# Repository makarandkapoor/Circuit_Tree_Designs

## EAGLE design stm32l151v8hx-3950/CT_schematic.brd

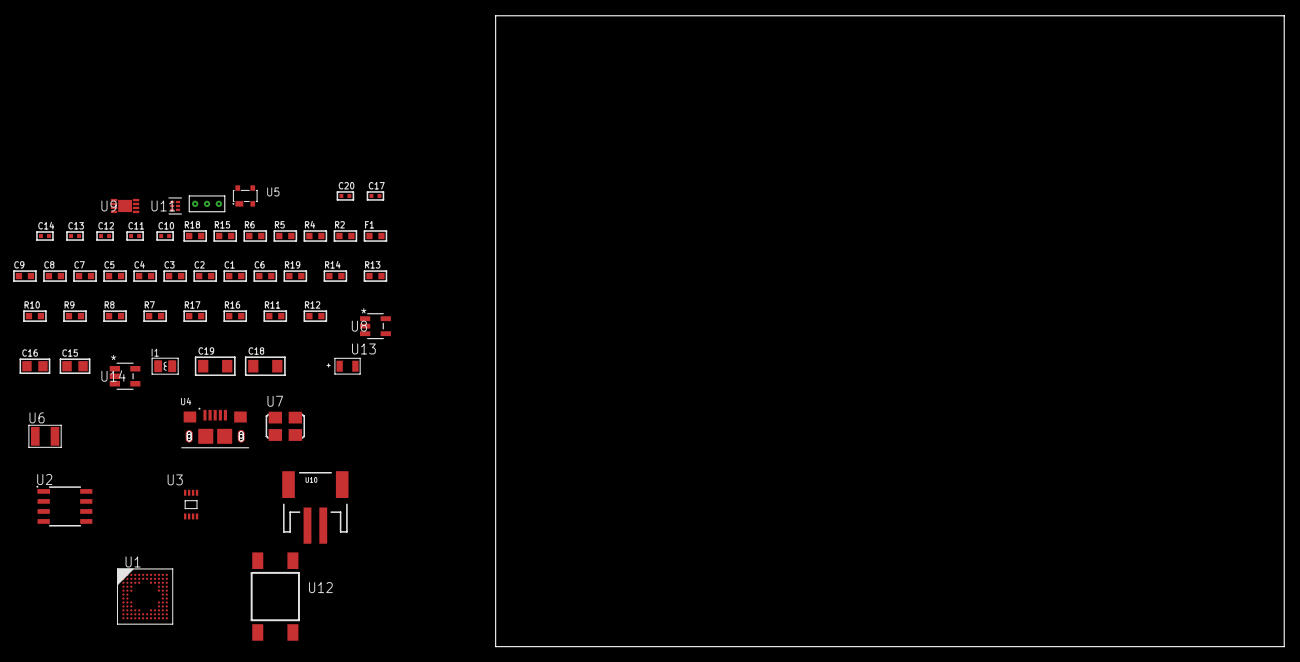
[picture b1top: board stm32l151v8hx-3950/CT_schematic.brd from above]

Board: 2 copper layers, 54 parts (0 on the bottom side), 32 nets, no tracks yet.

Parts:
C1, C2, C3, C4, C5, C7: 1e-07; C0603
C6: 4.7e-06; C0603
C8: 1e-08; C0603
C9: 1e-06; C0603
C10, C11: 1e-11; C0402
C12, C13, C14, C20: 1e-08; C0402
C15, C16: 1e-05; C0805
C17: 1e-07; C0402
C18, C19: 1e-05; C1206
F1: 240.0; L0603
I1: 3.3e-06; L0806
R2: 1000.0; R0603
R4: 4700.0; R0603
R5, R6: 2200.0; R0603
R7, R8, R9, R10, R13, R14, R19: 10000.0; R0603
R11: 220000.0; R0603
R12: 1000000.0; R0603
R15: 9100.0; R0603
R16: 680000.0; R0603
R17: 120000.0; R0603
R18: 2000.0; R0603
U1: STM32L151V8H6; UFBGA100
U2: AT25256B-SSHL-T; SOIC-8
U3: 24AA01T-I/MNY; TDFN-8/6MM
U4: 10118193-0001LF; FCI_10118193-0001LF
U5: prtr5v0u2ax; SOT143B
U6: ABS07-32.768KHZ-7-T
U7: ASFL1-25MHZ-NCS; ASFL1
U8: ltc3406es5; TSOT-23-5
U9: MCP73831T-2ACI/MC; DFN8_2X3MC
U10: S2B-PH-SM4-TB(LF)(SN); JST-2-SMD
U11: TPS3895ADRYR; SON-6
U12: 4-1437565-2; SW_4-1437565-2
U13: Q65110A2395; LGM67K-G1J2-24-Z
U14: nc7sz125m5x; NC7SZ125M5X
U15: Dummy; DUMMY_PACKAGE_120

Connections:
CLK_CRYSTAL_U1_D1: C10.1, U1.D1, U6.1
CLK_CRYSTAL_U1_E1: C11.1, U1.E1, U6.2
CLK_U1_F1: U1.F1, U7.3
GND: C1.2, C2.2, C3.2, C4.2, C5.2, C6.2, C7.2, C8.2, C9.2, C10.2, C11.2, C12.2, C13.2, C14.2, C15.2, C16.1, C16.2, C17.2, C18.2, C19.2, C20.2, R2.2, R7.2, R11.2, R15.2, R17.2, R18.2, U1.D3, U1.E3, U1.F2, U1.F11, U1.F12, U1.J1, U1.K1, U2.4, U3.4, U3.7, U4.5, U4.6, U4.7, U4.8, U4.9, U5.1, U7.2, U8.2, U9.6, U9.9, U10.2, U11.2, U13.C, U14.1, U14.3, U15.1
INPUT_USBPOWER_5V: C18.1, R19.2, U4.1, U5.4, U9.1, U9.2
NET_U1_A3: R5.1, U1.A3, U3.6
NET_U1_A4: R7.1, U1.A4
NET_U1_B3: R6.1, U1.B3, U3.5
NET_U1_E2: C7.1, U1.E2
NET_U1_H2: R4.1, U1.H2, U14.4
NET_U1_M1: C8.1, C9.1, F1.1, U1.L1, U1.M1
NET_U1_M12: U12.3, U12.4
NET_U2_3: R8.1, U2.3
NET_U2_7: R10.1, U2.7
NET_U8_3: I1.1, U8.3
NET_U8_5: R11.1, R12.1, U8.5
NET_U8_ATNET_3: I1.2, R12.2
NET_U9_5: R19.1, U9.5
NET_U9_8: R18.1, U9.8
NET_U11_1: R14.1, R15.1, U11.1
NET_U11_3: R16.2, R17.1, U11.3
NET_U11_4: R13.1, U11.4, U14.2
NET_U12_1: R2.1, U12.1, U12.2
PROC_ADC_IN20: U1.K11, U15.2
PROC_SPI1_MISO: U1.A7, U2.2
PROC_SPI1_MOSI: U1.C5, U2.5
PROC_SPI1_NSS: R9.1, U1.A9, U2.1
PROC_SPI1_SCK: U1.A8, U2.6
PROC_USB_DM: U1.B12, U4.2, U5.3
PROC_USB_DP: U1.A12, U4.3, U5.2
VCC_S1_3V7: C15.1, C19.1, U8.4, U9.3, U9.4, U10.1
VCC_TIER1_3V3: C1.1, C2.1, C3.1, C4.1, C5.1, C6.1, C12.1, C13.1, C14.1, C16.2, C17.1, C20.1, F1.2, I1.2, R4.2, R5.2, R6.2, R8.2, R9.2, R10.2, R12.2, R13.2, R14.2, R16.1, U1.C4, U1.G2, U1.G11, U1.G12, U1.H3, U2.8, U3.8, U7.4, U11.6, U14.5

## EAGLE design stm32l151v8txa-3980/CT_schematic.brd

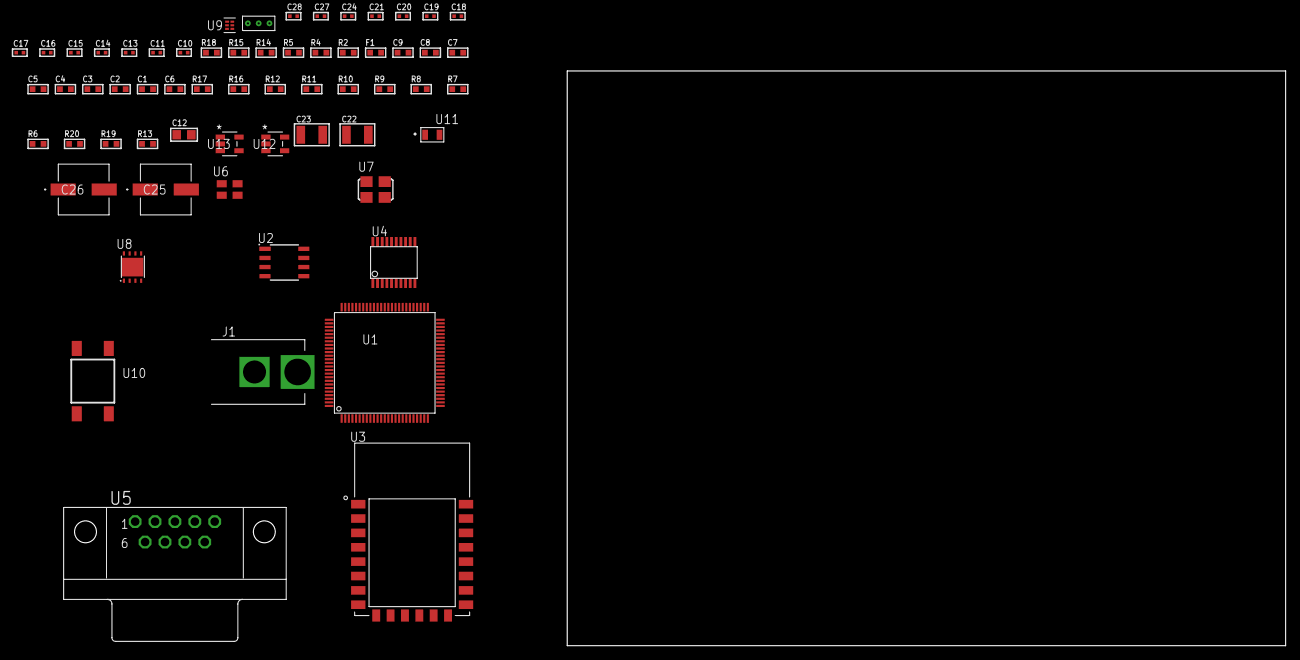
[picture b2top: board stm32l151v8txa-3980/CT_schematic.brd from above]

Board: 2 copper layers, 100.0 x 80.0 mm, 62 parts (0 on the bottom side), 46 nets, no tracks yet.

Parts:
C1, C2, C3, C4, C5, C7: 1e-07; C0603
C6: 4.7e-06; C0603
C8: 1e-08; C0603
C9: 1e-06; C0603
C10, C19, C20, C21, C27, C28: 1e-08; C0402
C11, C13, C14, C15, C16, C17, C18, C24: 1e-07; C0402
C12: 1e-05; C0805
C22, C23: 1e-05; C1210
C25, C26: 0.0001; EXV-9H
F1: 240.0; L0603
J1: PJ-037B; PJ-037B_PACKAGE
R2, R15: 1000.0; R0603
R4, R5: 4700.0; R0603
R6, R7, R8, R9, R10, R11, R12, R16, R17: 10000.0; R0603
R13: 100000.0; R0603
R14: 2231.0; R0603
R18: 9100.0; R0603
R19: 680000.0; R0603
R20: 120000.0; R0603
U1: STM32L151V8T6A; LQFP100
U2: AT25128B-SSHL-T; SOIC-8
U3: ESP8266-12E
U4: SP3203ECY-L/TR; TSSOP20-I
U5: 182-009-113R531; 182-009-MALE
U6: ASEK-32.768KHz-ECST; ASEK
U7: ASFL1-25MHZ-NCS; ASFL1
U8: LP3878SDX-ADJ/NOPB; WSON-8
U9: TPS3895ADRYR; SON-6
U10: 4-1437565-2; SW_4-1437565-2
U11: Q65110A2395; LGM67K-G1J2-24-Z
U12, U13: nc7sz125m5x; NC7SZ125M5X
U14: Dummy; DUMMY_PACKAGE_135

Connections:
CLK_U1_8: U1.8, U6.3
CLK_U1_12: U1.12, U7.3
GND: C1.2, C2.2, C3.2, C4.2, C5.2, C6.2, C7.2, C8.2, C9.2, C10.2, C11.2, C12.2, C13.2, C14.2, C17.2, C18.2, C19.2, C20.2, C21.2, C22.2, C23.2, C24.2, C25.2, C26.2, C27.2, C28.2, J1.2, R2.2, R6.2, R12.2, R15.2, R18.2, R20.2, U1.10, U1.19, U1.20, U1.27, U1.49, U1.74, U1.99, U2.4, U3.15, U4.18, U5.5, U6.2, U7.2, U8.3, U8.PAD, U9.2, U11.C, U12.1, U12.3, U13.1, U13.3, U14.1
NET_U1_6: C7.1, U1.6
NET_U1_14: R5.1, U1.14, U13.4
NET_U1_22: C8.1, C9.1, F1.1, U1.21, U1.22
NET_U1_94: R6.1, U1.94
NET_U1_98: U10.3, U10.4
NET_U2_3: R7.1, U2.3
NET_U2_7: R9.1, U2.7
NET_U3_1: R4.1, U3.1, U12.4
NET_U3_3: R10.1, U3.3
NET_U3_18: R11.1, U3.18
NET_U4_1: C15.1, U4.1
NET_U4_2: C17.1, U4.2
NET_U4_3: C15.2, U4.3
NET_U4_4: C16.1, U4.4
NET_U4_5: C16.2, U4.5
NET_U4_6: C18.1, U4.6
NET_U5_2: U4.14, U5.2
NET_U5_3: U4.17, U5.3
NET_U5_7: U4.13, U5.7
NET_U5_8: U4.16, U5.8
NET_U8_1: C21.1, U8.1
NET_U8_6: R14.2, R15.1, U8.6
NET_U8_8: R13.1, U8.8
NET_U9_1: R17.1, R18.1, U9.1
NET_U9_3: R19.2, R20.1, U9.3
NET_U9_4: R16.1, U9.4, U12.2, U13.2
NET_U10_1: R2.1, U10.1, U10.2
PROC_SPI1_MISO: U1.31, U3.6
PROC_SPI1_MOSI: U1.32, U3.7
PROC_SPI1_NSS: R12.1, U1.29, U3.16
PROC_SPI1_SCK: U1.30, U3.5
PROC_SPI2_MISO: U1.53, U2.2
PROC_SPI2_MOSI: U1.54, U2.5
PROC_SPI2_NSS: R8.1, U1.51, U2.1
PROC_SPI2_SCK: U1.52, U2.6
PROC_TIM2_CH1: U1.23, U14.3
PROC_TIM2_CH3: U1.25, U14.2
PROC_USART1_CTS: U1.70, U4.8
PROC_USART1_RTS: U1.71, U4.10
PROC_USART1_RX: U1.69, U4.11
PROC_USART1_TX: U1.68, U4.7
VCC_S1_15V4: C22.1, C25.1, C26.1, J1.1, R13.2, U8.4
VCC_TIER1_3V3: C1.1, C2.1, C3.1, C4.1, C5.1, C6.1, C10.1, C11.1, C12.1, C13.1, C14.1, C19.1, C20.1, C23.1, C24.1, C27.1, C28.1, F1.2, R4.2, R5.2, R7.2, R8.2, R9.2, R10.2, R11.2, R14.1, R16.2, R17.2, R19.1, U1.11, U1.28, U1.50, U1.75, U1.100, U2.8, U3.8, U4.12, U4.19, U6.4, U7.4, U8.5, U9.6, U12.5, U13.5

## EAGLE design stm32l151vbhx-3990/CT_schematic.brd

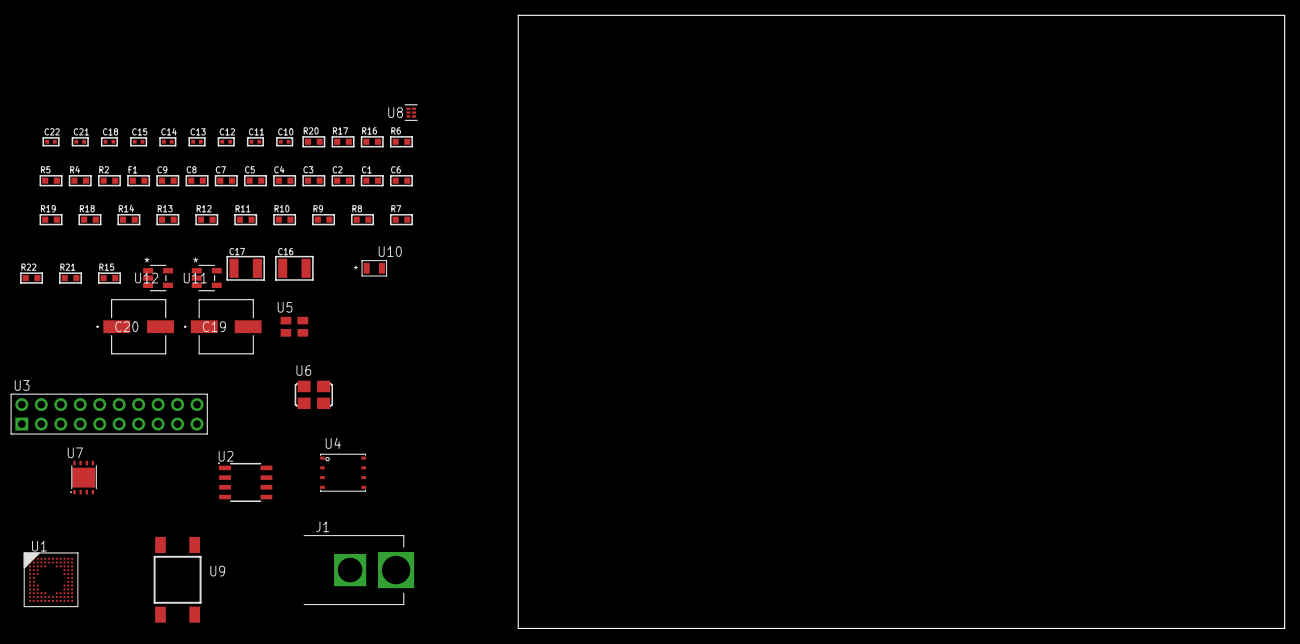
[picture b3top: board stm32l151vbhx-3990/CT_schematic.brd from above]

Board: 2 copper layers, 100.0 x 80.0 mm, 56 parts (0 on the bottom side), 32 nets, no tracks yet.

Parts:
C1, C2, C3, C4, C5, C7: 1e-07; C0603
C6: 4.7e-06; C0603
C8: 1e-08; C0603
C9: 1e-06; C0603
C10, C12, C13, C14, C15, C21, C22: 1e-08; C0402
C11, C18: 1e-07; C0402
C16, C17: 1e-05; C1210
C19, C20: 0.0001; EXV-9H
F1: 240.0; L0603
J1: PJ-037B; PJ-037B_PACKAGE
R2, R17: 1000.0; R0603
R4: 4700.0; R0603
R5, R6: 2200.0; R0603
R7, R8, R9, R10, R11, R12, R13, R14, R18, R19: 10000.0; R0603
R15: 100000.0; R0603
R16: 2231.0; R0603
R20: 9100.0; R0603
R21: 680000.0; R0603
R22: 120000.0; R0603
U1: STM32L151VBH6; UFBGA100
U2: AT25512N-SH-T; SOIC-8
U3: TST-110-05-T-D-RA
U4: 24AA256-I/MF; DFN8-S
U5: ASEK-32.768KHz-ECST; ASEK
U6: ASFL1-25MHZ-NCS; ASFL1
U7: LP3878SDX-ADJ/NOPB; WSON-8
U8: TPS3895ADRYR; SON-6
U9: 4-1437565-2; SW_4-1437565-2
U10: Q65110A2395; LGM67K-G1J2-24-Z
U11, U12: nc7sz125m5x; NC7SZ125M5X

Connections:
CLK_U1_D1: U1.D1, U5.3
CLK_U1_F1: U1.F1, U6.3
GND: C1.2, C2.2, C3.2, C4.2, C5.2, C6.2, C7.2, C8.2, C9.2, C10.2, C11.2, C12.2, C13.2, C14.2, C15.2, C16.2, C17.2, C18.2, C19.2, C20.2, C21.2, C22.2, J1.2, R2.2, R7.2, R14.2, R17.2, R20.2, R22.2, U1.D3, U1.E3, U1.F2, U1.F11, U1.F12, U1.J1, U1.K1, U2.4, U3.4, U3.6, U3.8, U3.10, U3.12, U3.14, U3.16, U3.18, U3.20, U4.4, U4.7, U5.2, U6.2, U7.3, U7.PAD, U8.2, U10.C, U11.2, U11.3, U12.1, U12.3
NET_U1_A3: R5.1, U1.A3, U4.6
NET_U1_A4: R7.1, U1.A4
NET_U1_B3: R6.1, U1.B3, U4.5
NET_U1_E2: C7.1, U1.E2
NET_U1_H2: R4.1, U1.H2, U12.4
NET_U1_M1: C8.1, C9.1, F1.1, U1.L1, U1.M1
NET_U1_M12: U9.3, U9.4
NET_U2_3: R8.1, U2.3
NET_U2_7: R10.1, U2.7
NET_U4_1: R12.1, U4.1
NET_U4_2: R13.1, U4.2
NET_U4_3: R14.1, U4.3
NET_U7_1: C15.1, U7.1
NET_U7_6: R16.2, R17.1, U7.6
NET_U7_8: R15.1, U7.8
NET_U8_1: R19.1, R20.1, U8.1
NET_U8_3: R21.2, R22.1, U8.3
NET_U8_4: R18.1, U8.4, U11.4, U12.2
NET_U9_1: R2.1, U9.1, U9.2
PROC_SPI1_MISO: U1.A7, U2.2
PROC_SPI1_MOSI: U1.A12, U2.5
PROC_SPI1_NSS: R9.1, U1.A9, U2.1
PROC_SPI1_SCK: U1.K4, U2.6
PROC_SYS_JTCK_SWCLK: U1.A10, U3.9
PROC_SYS_JTDO_TRACESWO: U1.A8, U3.13
PROC_SYS_JTMS_SWDIO: U1.A11, U3.7
RST_OUT_U3_SRESET_B: R11.1, U3.15, U11.1
VCC_S1_11V8: C16.1, C19.1, C20.1, J1.1, R15.2, U7.4
VCC_TIER1_3V3: C1.1, C2.1, C3.1, C4.1, C5.1, C6.1, C10.1, C11.1, C12.1, C13.1, C14.1, C17.1, C18.1, C21.1, C22.1, F1.2, R4.2, R5.2, R6.2, R8.2, R9.2, R10.2, R11.2, R12.2, R13.2, R16.1, R18.2, R19.2, R21.1, U1.C4, U1.G2, U1.G11, U1.G12, U1.H3, U2.8, U3.1, U4.8, U5.4, U6.4, U7.5, U8.6, U11.5, U12.5

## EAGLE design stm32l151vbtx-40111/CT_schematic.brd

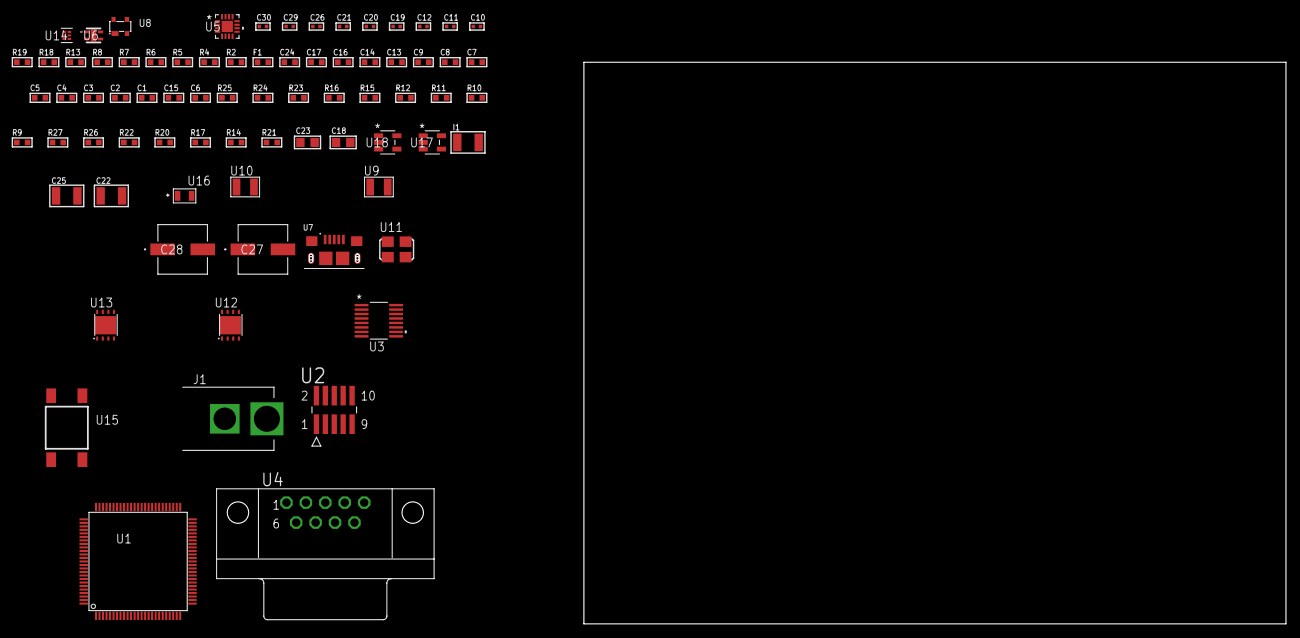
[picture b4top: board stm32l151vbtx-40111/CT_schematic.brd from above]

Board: 2 copper layers, 76 parts (0 on the bottom side), 50 nets, no tracks yet.

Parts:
C1, C2, C3, C4, C5, C7: 1e-07; C0603
C6: 4.7e-06; C0603
C8: 1e-08; C0603
C9, C13, C14, C16, C17: 1e-06; C0603
C10, C11: 1e-11; C0402
C12, C19, C26: 1e-07; C0402
C15: 2.2e-07; C0603
C18: 4.7e-06; C0805
C20, C21, C29, C30: 1e-08; C0402
C22, C25: 1e-05; C1210
C23: 1e-05; C0805
C24: 8e-07; R0603
C27, C28: 0.0001; EXV-9H
F1: 240.0; L0603
I1: 1e-05; L1210
J1: PJ-037B; PJ-037B_PACKAGE
R2, R19: 1000.0; R0603
R4: 4700.0; R0603
R5, R6, R7, R8: 2200.0; R0603
R9, R10, R11, R12, R15, R16, R23, R24: 10000.0; R0603
R13: 5.0; R0603
R14, R17, R20, R22: 100000.0; R0603
R18: 806.0; R0603
R21: 153694.38; R0603
R25: 82000.0; R0603
R26: 300000.0; R0603
R27: 120000.0; R0603
U1: STM32L151VBT6; LQFP100
U2: FTSH-105-01-L-DV-K; SAMTEC_FTSH-105-01-L-DV-K
U3: LTC2804CGN-1#PBF; SSOP-16
U4: 182-009-113R531; 182-009-MALE
U5: M41T65Q6F; M41T65_QFN-16
U6: Si7034-A10-IM; SI7034-A10-IM
U7: 10118193-0001LF; FCI_10118193-0001LF
U8: prtr5v0u2ax; SOT143B
U9, U10: ABS07-32.768KHZ-7-T
U11: ASFL1-25MHZ-NCS; ASFL1
U12: LP3878SDX-ADJ/NOPB; WSON-8
U13: LP2951ACSDX/NOPB; WSON-8
U14: TPS3895ADRYR; SON-6
U15: 4-1437565-2; SW_4-1437565-2
U16: Q65110A2395; LGM67K-G1J2-24-Z
U17, U18: nc7sz125m5x; NC7SZ125M5X

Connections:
CLK_CRYSTAL_U1_8: C10.1, U1.8, U10.1
CLK_CRYSTAL_U1_9: C11.1, U1.9, U10.2
CLK_CRYSTAL_U5_1: U5.1, U9.1
CLK_CRYSTAL_U5_2: U5.2, U9.2
CLK_U1_12: U1.12, U11.3
GND: C1.2, C2.2, C3.2, C4.2, C5.2, C6.2, C7.2, C8.2, C9.2, C10.2, C11.2, C12.2, C13.2, C14.2, C16.2, C17.2, C18.2, C19.2, C20.2, C21.2, C22.2, C23.2, C24.2, C25.2, C26.2, C27.2, C28.2, C29.2, C30.2, J1.2, R2.2, R9.2, R13.2, R19.2, R22.2, R25.2, R27.2, U1.10, U1.19, U1.20, U1.27, U1.49, U1.74, U1.99, U2.3, U2.5, U3.8, U4.5, U5.3, U5.5, U5.17, U6.5, U7.5, U7.6, U7.7, U7.8, U7.9, U8.1, U11.2, U12.3, U12.PAD, U13.3, U13.4, U13.PAD, U14.2, U16.C, U17.2, U17.3, U18.1, U18.3
NET_U1_6: C7.1, U1.6
NET_U1_14: R4.1, U1.14, U18.4
NET_U1_22: C8.1, C9.1, F1.1, U1.21, U1.22
NET_U1_47: R7.1, U1.47, U6.2
NET_U1_48: R8.1, U1.48, U6.4
NET_U1_92: R5.1, U1.92, U5.10
NET_U1_93: R6.1, U1.93, U5.9
NET_U1_94: R9.1, U1.94
NET_U1_98: U15.3, U15.4
NET_U2_9: R13.1, U2.9
NET_U3_6: C13.1, U3.6
NET_U3_7: C15.1, I1.2, U3.7
NET_U3_9: C14.1, U3.9
NET_U3_10: C15.2, U3.10
NET_U3_11: R14.1, U3.11
NET_U4_2: U3.1, U4.2
NET_U4_3: U3.3, U4.3
NET_U4_7: U3.2, U4.7
NET_U4_8: U3.4, U4.8
NET_U5_4: R15.1, U5.4
NET_U5_11: R16.1, U5.11
NET_U8_4: U7.1, U8.4
NET_U12_1: C21.1, U12.1
NET_U12_6: R18.2, R19.1, U12.6
NET_U12_8: R17.1, U12.8
NET_U13_5: R20.1, U13.5
NET_U13_7: R21.2, R22.1, U13.7
NET_U14_1: R24.1, R25.1, U14.1
NET_U14_3: R26.2, R27.1, U14.3
NET_U14_4: R23.1, U14.4, U17.4, U18.2
NET_U15_1: R2.1, U15.1, U15.2
PROC_SYS_JTCK_SWCLK: R11.1, U1.76, U2.4
PROC_SYS_JTDO_TRACESWO: U1.89, U2.6
PROC_SYS_JTMS_SWDIO: R12.1, U1.72, U2.2
PROC_USART2_CTS: U1.23, U3.13
PROC_USART2_RTS: U1.24, U3.15
PROC_USART2_RX: U1.26, U3.16
PROC_USART2_TX: U1.25, U3.14
PROC_USB_DM: U1.70, U7.2, U8.3
PROC_USB_DP: U1.71, U7.3, U8.2
RST_OUT_U2_JTAG_RST_B: R10.1, U2.10, U17.1
VCC_S1_15V1: C22.1, C24.1, C27.1, C28.1, J1.1, R17.2, U12.4, U13.8
VCC_TIER1_1V8: C1.1, C2.1, C3.1, C4.1, C5.1, C6.1, C12.1, C16.1, C17.1, C18.1, C19.1, C23.1, C26.1, C29.1, C30.1, F1.2, I1.1, R4.2, R5.2, R6.2, R7.2, R8.2, R10.2, R11.2, R12.2, R14.2, R15.2, R16.2, R18.1, R23.2, R24.2, R26.1, U1.11, U1.28, U1.50, U1.75, U1.100, U2.1, U3.5, U3.12, U5.14, U6.1, U12.5, U14.6, U17.5, U18.5
VCC_TIER1_3V3: C20.1, C25.1, R20.2, R21.1, U11.4, U13.1

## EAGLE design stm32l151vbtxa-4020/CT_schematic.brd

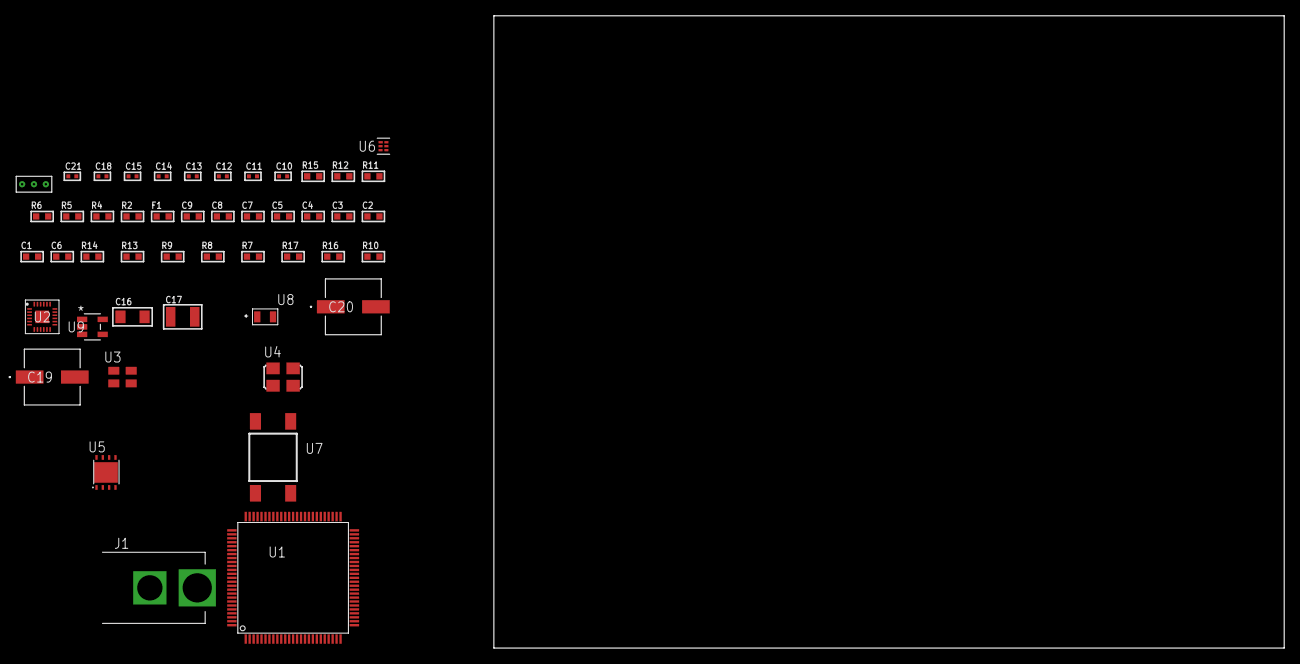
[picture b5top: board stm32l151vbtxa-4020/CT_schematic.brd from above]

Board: 2 copper layers, 100.0 x 80.0 mm, 48 parts (0 on the bottom side), 26 nets, no tracks yet.

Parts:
C1, C2, C3, C4, C5, C7: 1e-07; C0603
C6: 4.7e-06; C0603
C8: 1e-08; C0603
C9: 1e-06; C0603
C10, C11, C18: 1e-07; C0402
C12, C13, C14, C15, C21: 1e-08; C0402
C16: 1e-05; C1206
C17: 1e-05; C1210
C19, C20: 0.0001; EXV-9H
F1: 240.0; L0603
J1: PJ-037B; PJ-037B_PACKAGE
R2, R12: 1000.0; R0603
R4: 4700.0; R0603
R5, R6: 2200.0; R0603
R7, R8, R9, R13, R14: 10000.0; R0603
R10: 100000.0; R0603
R11: 2231.0; R0603
R15: 9100.0; R0603
R16: 680000.0; R0603
R17: 120000.0; R0603
U1: STM32L151VBT6A; LQFP100
U2: MPU-9250; QFN24_2
U3: ASEK-32.768KHz-ECST; ASEK
U4: ASFL1-25MHZ-NCS; ASFL1
U5: LP3878SDX-ADJ/NOPB; WSON-8
U6: TPS3895ADRYR; SON-6
U7: 4-1437565-2; SW_4-1437565-2
U8: Q65110A2395; LGM67K-G1J2-24-Z
U9: nc7sz125m5x; NC7SZ125M5X
U10: Dummy; DUMMY_PACKAGE_106

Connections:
CLK_U1_8: U1.8, U3.3
CLK_U1_12: U1.12, U4.3
GND: C1.2, C2.2, C3.2, C4.2, C5.2, C6.2, C7.2, C8.2, C9.2, C10.2, C11.2, C12.2, C13.2, C14.2, C15.2, C16.2, C17.2, C18.2, C19.2, C20.2, C21.2, J1.2, R2.2, R7.2, R9.2, R12.2, R15.2, R17.2, U1.10, U1.19, U1.20, U1.27, U1.49, U1.74, U1.99, U2.18, U2.20, U2.25, U3.2, U4.2, U5.3, U5.PAD, U6.2, U8.C, U9.1, U9.3, U10.1
NET_U1_6: C7.1, U1.6
NET_U1_14: R4.1, U1.14, U9.4
NET_U1_22: C8.1, C9.1, F1.1, U1.21, U1.22
NET_U1_92: R5.1, U1.92, U2.23
NET_U1_93: R6.1, U1.93, U2.24
NET_U1_94: R7.1, U1.94
NET_U1_98: U7.3, U7.4
NET_U2_9: R9.1, U2.9
NET_U2_10: C10.1, U2.10
NET_U2_22: R8.1, U2.22
NET_U5_1: C15.1, U5.1
NET_U5_6: R11.2, R12.1, U5.6
NET_U5_8: R10.1, U5.8
NET_U6_1: R14.1, R15.1, U6.1
NET_U6_3: R16.2, R17.1, U6.3
NET_U6_4: R13.1, U6.4, U9.2
NET_U7_1: R2.1, U7.1, U7.2
PROC_ADC_IN20: U1.53, U10.2
PROC_ADC_IN22: U1.38, U10.3
PROC_GPIO_TO_U2_FSYNC: U1.2, U2.11
PROC_GPIO_TO_U2_INT_B: U1.1, U2.12
VCC_S1_5V9: C16.1, C19.1, C20.1, J1.1, R10.2, U5.4
VCC_TIER1_3V3: C1.1, C2.1, C3.1, C4.1, C5.1, C6.1, C11.1, C12.1, C13.1, C14.1, C17.1, C18.1, C21.1, F1.2, R4.2, R5.2, R6.2, R8.2, R11.1, R13.2, R14.2, R16.1, U1.11, U1.28, U1.50, U1.75, U1.100, U2.1, U2.8, U2.13, U3.4, U4.4, U5.5, U6.6, U9.5

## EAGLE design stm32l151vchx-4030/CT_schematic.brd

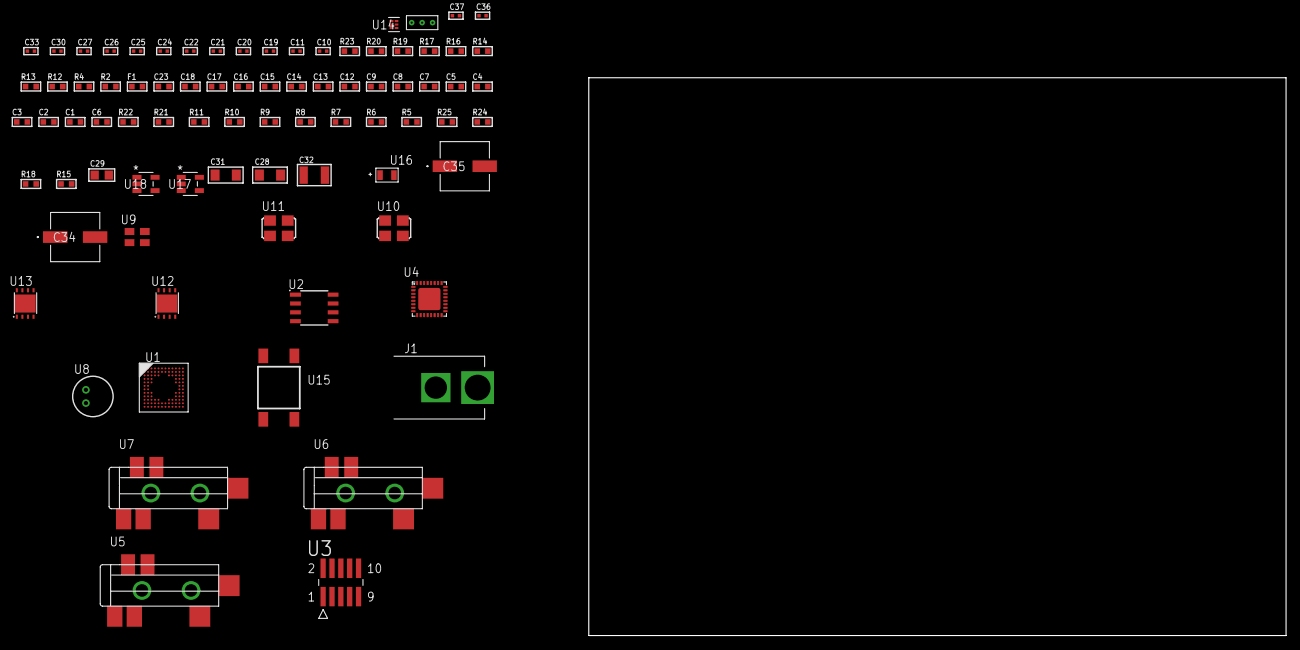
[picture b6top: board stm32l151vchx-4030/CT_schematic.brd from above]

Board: 2 copper layers, 100.0 x 80.0 mm, 81 parts (0 on the bottom side), 51 nets, no tracks yet.

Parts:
C1, C2, C3, C4, C5, C7: 1e-07; C0603
C6: 4.7e-06; C0603
C8: 1e-08; C0603
C9, C12, C13, C14, C15, C16, C17, C18, C23: 1e-06; C0603
C10, C24, C25, C26, C27, C30, C36, C37: 1e-08; C0402
C11, C19, C20, C21, C22, C33: 1e-07; C0402
C28, C31: 1e-05; C1206
C29: 1e-05; C0805
C32: 1e-05; C1210
C34, C35: 0.0001; EXV-9H
F1: 240.0; L0603
J1: PJ-037B; PJ-037B_PACKAGE
R2, R17, R20: 1000.0; R0603
R4: 4700.0; R0603
R5, R6, R7, R8, R9, R10, R11, R21, R22: 10000.0; R0603
R12: 5.0; R0603
R13, R14: 1270.0; R0603
R15, R18: 100000.0; R0603
R16: 200.0; R0603
R19: 2231.0; R0603
R23: 9100.0; R0603
R24: 680000.0; R0603
R25: 120000.0; R0603
U1: STM32L151VCH6; UFBGA100
U2: AT25080B-SSHL-T; SOIC-8
U3: FTSH-105-01-L-DV-K; SAMTEC_FTSH-105-01-L-DV-K
U4: SGTL5000XNAA3; QFN-32
U5, U6, U7: SJ-43515TS-SMT-TR
U8: WM-64PCT; WM-64PC
U9: ASEK-32.768KHz-ECST; ASEK
U10: ASFL-24.57MHZ-NCS; ASFL1
U11: ASFL1-25MHZ-NCS; ASFL1
U12, U13: LP3878SDX-ADJ/NOPB; WSON-8
U14: TPS3895ADRYR; SON-6
U15: 4-1437565-2; SW_4-1437565-2
U16: Q65110A2395; LGM67K-G1J2-24-Z
U17, U18: nc7sz125m5x; NC7SZ125M5X
U19: Dummy; DUMMY_PACKAGE_172

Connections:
CLK_U1_D1: U1.D1, U9.3
CLK_U1_F1: U1.F1, U11.3
CLK_U4_21: U4.21, U10.3
GND: C1.2, C2.2, C3.2, C4.2, C5.2, C6.2, C7.2, C8.2, C9.2, C10.2, C11.2, C19.2, C20.2, C21.2, C22.2, C23.2, C24.2, C25.2, C26.2, C27.2, C28.2, C29.2, C30.2, C31.2, C32.2, C33.2, C34.2, C35.2, C36.2, C37.2, J1.2, R2.2, R5.2, R12.2, R14.2, R17.2, R20.2, R23.2, R25.2, U1.D3, U1.E3, U1.F2, U1.F11, U1.F12, U1.J1, U1.K1, U2.4, U3.3, U3.5, U4.1, U4.3, U4.7, U4.EXP, U6.1, U7.1, U8.2, U9.2, U10.2, U11.2, U12.3, U12.PAD, U13.3, U13.PAD, U14.2, U16.C, U17.2, U17.3, U18.1, U18.3, U19.1
NET_U1_A4: R5.1, U1.A4
NET_U1_E2: C7.1, U1.E2
NET_U1_H2: R4.1, U1.H2, U18.4
NET_U1_M1: C8.1, C9.1, F1.1, U1.L1, U1.M1
NET_U1_M12: U15.3, U15.4
NET_U2_3: R6.1, U2.3
NET_U2_7: R8.1, U2.7
NET_U3_9: R12.1, U3.9
NET_U4_10: C22.1, U4.10
NET_U4_29: R13.1, U4.29
NET_U4_31: R14.1, U4.31
NET_U5_1: U4.4, U5.1
NET_U5_2: U4.2, U5.2
NET_U5_5: U4.6, U5.5
NET_U6_2: C13.1, U6.2
NET_U6_5: C12.1, U6.5
NET_U7_2: C15.1, C16.1, U7.2
NET_U7_5: C14.1, U7.5
NET_U7_13: C15.2, C16.2
NET_U8_1: C17.1, C18.1, C23.1, U4.16, U8.1
NET_U8_15: C17.2, C18.2
NET_U12_1: C27.1, U12.1
NET_U12_6: R16.2, R17.1, U12.6
NET_U12_8: R15.1, U12.8
NET_U13_1: C30.1, U13.1
NET_U13_6: R19.2, R20.1, U13.6
NET_U13_8: R18.1, U13.8
NET_U14_1: R22.1, R23.1, U14.1
NET_U14_3: R24.2, R25.1, U14.3
NET_U14_4: R21.1, U14.4, U17.4, U18.2
NET_U15_1: R2.1, U15.1, U15.2
PROC_I2S2_CK: U1.B9, U4.24
PROC_I2S2_SD: U1.B7, U4.26
PROC_I2S2_WS: U1.C9, U4.23
PROC_PE1: U1.A2, U19.3
PROC_PE3: U1.A1, U19.2
PROC_SPI1_MISO: U1.A7, U2.2
PROC_SPI1_MOSI: U1.A12, U2.5
PROC_SPI1_NSS: R7.1, U1.A9, U2.1
PROC_SPI1_SCK: U1.K4, U2.6
PROC_SYS_JTCK_SWCLK: R10.1, U1.A10, U3.4
PROC_SYS_JTDO_TRACESWO: U1.A8, U3.6
PROC_SYS_JTMS_SWDIO: R11.1, U1.A11, U3.2
RST_OUT_U3_JTAG_RST_B: R9.1, U3.10, U17.1
VCC_S1_9V9: C28.1, C31.1, C34.1, C35.1, J1.1, R15.2, R18.2, U12.4, U13.4
VCC_TIER1_1V2: C19.1, C29.1, R16.1, U4.30, U12.5
VCC_TIER1_3V3: C1.1, C2.1, C3.1, C4.1, C5.1, C6.1, C10.1, C11.1, C20.1, C21.1, C24.1, C25.1, C26.1, C32.1, C33.1, C36.1, C37.1, F1.2, R4.2, R6.2, R7.2, R8.2, R9.2, R10.2, R11.2, R13.2, R19.1, R21.2, R22.2, R24.1, U1.C4, U1.G2, U1.G11, U1.G12, U1.H3, U2.8, U3.1, U4.5, U4.20, U9.4, U10.4, U11.4, U13.5, U14.6, U17.5, U18.5

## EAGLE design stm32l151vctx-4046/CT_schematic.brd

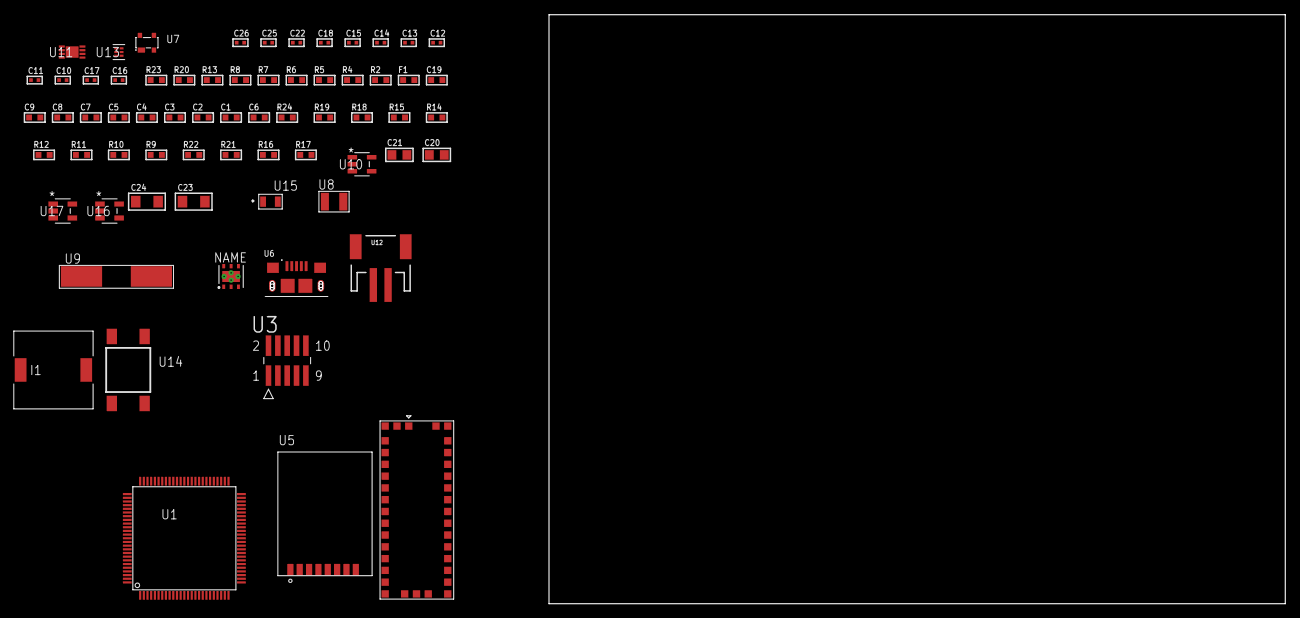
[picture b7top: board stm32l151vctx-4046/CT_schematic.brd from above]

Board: 2 copper layers, 67 parts (0 on the bottom side), 38 nets, no tracks yet.

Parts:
C1, C2, C3, C4, C5, C7: 1e-07; C0603
C6: 4.7e-06; C0603
C8: 1e-08; C0603
C9, C19: 1e-06; C0603
C10, C11, C12, C13: 1e-11; C0402
C14, C25, C26: 1e-08; C0402
C15, C18, C22: 1e-07; C0402
C16, C17: 2.2e-11; C0402
C20, C21: 1e-05; C0805
C23, C24: 1e-05; C1206
F1: 240.0; L0603
I1: 2.5e-06; DR1040
R2: 1000.0; R0603
R4: 4700.0; R0603
R5, R6, R7, R8: 2200.0; R0603
R9, R10, R11, R12, R14, R15, R18, R19, R24: 10000.0; R0603
R13: 5.0; R0603
R16: 220000.0; R0603
R17: 1000000.0; R0603
R20: 9100.0; R0603
R21: 680000.0; R0603
R22: 120000.0; R0603
R23: 2000.0; R0603
U1: STM32L151VCT6; LQFP100
U2: HDC1080DMBR; WSON-6
U3: FTSH-105-01-L-DV-K; SAMTEC_FTSH-105-01-L-DV-K
U4: M10382
U5: RFM75-S
U6: 10118193-0001LF; FCI_10118193-0001LF
U7: prtr5v0u2ax; SOT143B
U8: ABS07-32.768KHZ-7-T
U9: ABLS-25.000MHZ-B2F-T
U10: ltc3406es5; TSOT-23-5
U11: MCP73831T-2ACI/MC; DFN8_2X3MC
U12: S2B-PH-SM4-TB(LF)(SN); JST-2-SMD
U13: TPS3895ADRYR; SON-6
U14: 4-1437565-2; SW_4-1437565-2
U15: Q65110A2395; LGM67K-G1J2-24-Z
U16, U17: nc7sz125m5x; NC7SZ125M5X

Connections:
CLK_CRYSTAL_U1_8: C10.1, U1.8, U8.1
CLK_CRYSTAL_U1_9: C11.1, U1.9, U8.2
CLK_CRYSTAL_U1_12: C12.1, U1.12, U9.1
CLK_CRYSTAL_U1_13: C13.1, U1.13, U9.2
GND: C1.2, C2.2, C3.2, C4.2, C5.2, C6.2, C7.2, C8.2, C9.2, C10.2, C11.2, C12.2, C13.2, C14.2, C15.2, C16.2, C17.2, C18.2, C19.2, C20.2, C21.1, C21.2, C22.2, C23.2, C24.2, C25.2, C26.2, R2.2, R9.2, R13.2, R16.2, R20.2, R22.2, R23.2, U1.10, U1.19, U1.20, U1.27, U1.49, U1.74, U1.99, U2.2, U2.PAD, U3.3, U3.5, U4.2, U4.4, U4.14, U4.17, U4.21, U4.24, U4.26, U4.28, U4.33, U4.34, U4.35, U4.36, U5.1, U6.5, U6.6, U6.7, U6.8, U6.9, U7.1, U10.2, U11.6, U11.9, U12.2, U13.2, U15.C, U16.2, U16.3, U17.1, U17.3
INPUT_USBPOWER_5V: C23.1, R24.2, U6.1, U7.4, U11.1, U11.2
NET_U1_6: C7.1, U1.6
NET_U1_14: R4.1, U1.14, U17.4
NET_U1_22: C8.1, C9.1, F1.1, U1.21, U1.22
NET_U1_47: R7.1, U1.47, U2.6
NET_U1_48: R8.1, U1.48, U2.1
NET_U1_92: R5.1, U1.92, U4.19
NET_U1_93: R6.1, U1.93, U4.18
NET_U1_94: R9.1, U1.94
NET_U1_98: U14.3, U14.4
NET_U3_9: R13.1, U3.9
NET_U5_3: R14.1, U5.3
NET_U10_3: I1.1, U10.3
NET_U10_5: R16.1, R17.1, U10.5
NET_U10_ATNET_3: I1.2, R17.2
NET_U11_5: R24.1, U11.5
NET_U11_8: R23.1, U11.8
NET_U13_1: R19.1, R20.1, U13.1
NET_U13_3: R21.2, R22.1, U13.3
NET_U13_4: R18.1, U13.4, U16.4, U17.2
NET_U14_1: R2.1, U14.1, U14.2
PROC_SPI1_MISO: U1.31, U5.7
PROC_SPI1_MOSI: U1.32, U5.6
PROC_SPI1_NSS: R15.1, U1.29, U5.4
PROC_SPI1_SCK: U1.30, U5.5
PROC_SYS_JTCK_SWCLK: R11.1, U1.76, U3.4
PROC_SYS_JTDO_TRACESWO: U1.89, U3.6
PROC_SYS_JTMS_SWDIO: R12.1, U1.72, U3.2
PROC_USB_DM: U1.70, U6.2, U7.3
PROC_USB_DP: U1.71, U6.3, U7.2
RST_OUT_U3_JTAG_RST_B: R10.1, U3.10, U16.1
VCC_S1_3V7: C20.1, C24.1, U10.4, U11.3, U11.4, U12.1
VCC_TIER1_3V3: C1.1, C2.1, C3.1, C4.1, C5.1, C6.1, C14.1, C15.1, C16.1, C17.1, C18.1, C19.1, C21.2, C22.1, C25.1, C26.1, F1.2, I1.2, R4.2, R5.2, R6.2, R7.2, R8.2, R10.2, R11.2, R12.2, R14.2, R15.2, R17.2, R18.2, R19.2, R21.1, U1.11, U1.28, U1.50, U1.75, U1.100, U2.5, U3.1, U4.5, U4.25, U4.27, U5.2, U13.6, U16.5, U17.5

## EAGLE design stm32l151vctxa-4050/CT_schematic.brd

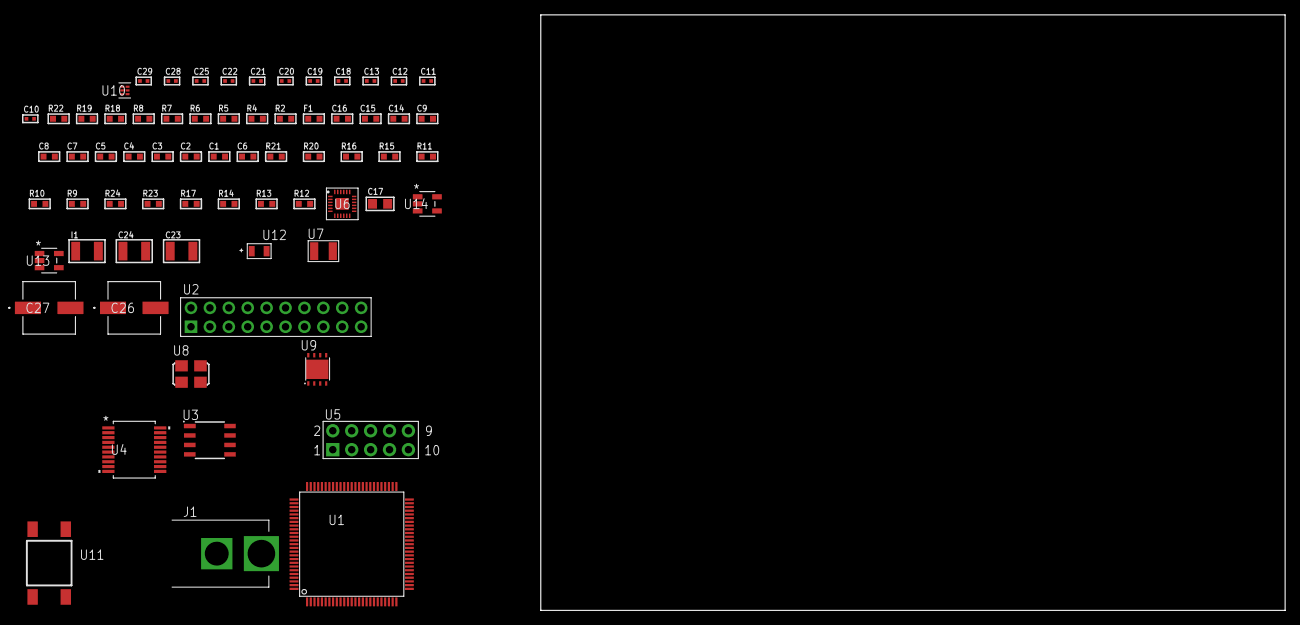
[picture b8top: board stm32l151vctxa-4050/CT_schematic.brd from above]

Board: 2 copper layers, 100.0 x 80.0 mm, 68 parts (0 on the bottom side), 48 nets, no tracks yet.

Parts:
C1, C2, C3, C4, C5, C7: 1e-07; C0603
C6: 4.7e-06; C0603
C8: 1e-08; C0603
C9, C14, C15, C16: 1e-06; C0603
C10, C11: 1e-11; C0402
C12, C18, C19, C25: 1e-07; C0402
C13, C20, C21, C22, C28, C29: 1e-08; C0402
C17: 4.7e-06; C0805
C23, C24: 1e-05; C1210
C26, C27: 0.0001; EXV-9H
F1: 240.0; L0603
I1: 1.5e-05; L1210
J1: PJ-037B; PJ-037B_PACKAGE
R2, R19: 1000.0; R0603
R4: 4700.0; R0603
R5, R6, R7, R8: 2200.0; R0603
R9, R10, R11, R15, R16, R20, R21: 10000.0; R0603
R12, R13, R14, R17: 100000.0; R0603
R18: 2231.0; R0603
R22: 9100.0; R0603
R23: 680000.0; R0603
R24: 120000.0; R0603
U1: STM32L151VCT6A; LQFP100
U2: TST-110-05-T-D-RA
U3: M24M02-DRMN6TP; SOIC-8
U4: MAX3218EAP+T; SSOP-20
U5: HTSS-105-01-G-D
U6: MPU-9250; QFN24_2
U7: ABS07-32.768KHZ-7-T
U8: ASFL1-25MHZ-NCS; ASFL1
U9: LP3878SDX-ADJ/NOPB; WSON-8
U10: TPS3895ADRYR; SON-6
U11: 4-1437565-2; SW_4-1437565-2
U12: Q65110A2395; LGM67K-G1J2-24-Z
U13, U14: nc7sz125m5x; NC7SZ125M5X

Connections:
CLK_CRYSTAL_U1_8: C10.1, U1.8, U7.1
CLK_CRYSTAL_U1_9: C11.1, U1.9, U7.2
CLK_U1_12: U1.12, U8.3
GND: C1.2, C2.2, C3.2, C4.2, C5.2, C6.2, C7.2, C8.2, C9.2, C10.2, C11.2, C12.2, C13.2, C14.2, C15.2, C16.2, C18.2, C19.2, C20.2, C21.2, C22.2, C23.2, C24.2, C25.2, C26.2, C27.2, C28.2, C29.2, J1.2, R2.2, R9.2, R11.2, R19.2, R22.2, R24.2, U1.10, U1.19, U1.20, U1.27, U1.49, U1.74, U1.99, U2.4, U2.6, U2.8, U2.10, U2.12, U2.14, U2.16, U2.18, U2.20, U3.4, U4.5, U4.17, U4.20, U5.9, U6.18, U6.20, U6.25, U8.2, U9.3, U9.PAD, U10.2, U12.C, U13.2, U13.3, U14.1, U14.3
NET_U1_6: C7.1, U1.6
NET_U1_14: R4.1, U1.14, U14.4
NET_U1_22: C8.1, C9.1, F1.1, U1.21, U1.22
NET_U1_47: R7.1, U1.47, U3.6
NET_U1_48: R8.1, U1.48, U3.5
NET_U1_92: R5.1, U1.92, U6.23
NET_U1_93: R6.1, U1.93, U6.24
NET_U1_94: R9.1, U1.94
NET_U1_98: U11.3, U11.4
NET_U3_3: R11.1, U3.3
NET_U4_1: I1.1, U4.1
NET_U4_2: R12.1, U4.2
NET_U4_3: R13.1, U4.3
NET_U4_4: R14.1, U4.4
NET_U4_15: C16.1, U4.15
NET_U4_16: C17.2, U4.16
NET_U4_18: C17.1, U4.18
NET_U4_19: C15.1, U4.19
NET_U5_3: U4.12, U5.3
NET_U5_4: U4.11, U5.4
NET_U5_5: U4.14, U5.5
NET_U5_6: U4.13, U5.6
NET_U6_9: R16.1, U6.9
NET_U6_10: C18.1, U6.10
NET_U6_22: R15.1, U6.22
NET_U9_1: C22.1, U9.1
NET_U9_6: R18.2, R19.1, U9.6
NET_U9_8: R17.1, U9.8
NET_U10_1: R21.1, R22.1, U10.1
NET_U10_3: R23.2, R24.1, U10.3
NET_U10_4: R20.1, U10.4, U13.4, U14.2
NET_U11_1: R2.1, U11.1, U11.2
PROC_GPIO_TO_U6_FSYNC: U1.2, U6.11
PROC_GPIO_TO_U6_INT_B: U1.1, U6.12
PROC_SYS_JTCK_SWCLK: U1.76, U2.9
PROC_SYS_JTDO_TRACESWO: U1.89, U2.13
PROC_SYS_JTMS_SWDIO: U1.72, U2.7
PROC_USART1_CTS: U1.70, U4.8
PROC_USART1_RTS: U1.71, U4.10
PROC_USART1_RX: U1.69, U4.9
PROC_USART1_TX: U1.68, U4.7
RST_OUT_U2_SRESET_B: R10.1, U2.15, U13.1
VCC_S1_12V5: C23.1, C26.1, C27.1, J1.1, R17.2, U9.4
VCC_TIER1_3V3: C1.1, C2.1, C3.1, C4.1, C5.1, C6.1, C12.1, C13.1, C14.1, C19.1, C20.1, C21.1, C24.1, C25.1, C28.1, C29.1, F1.2, I1.2, R4.2, R5.2, R6.2, R7.2, R8.2, R10.2, R12.2, R13.2, R14.2, R15.2, R16.2, R18.1, R20.2, R21.2, R23.1, U1.11, U1.28, U1.50, U1.75, U1.100, U2.1, U3.8, U4.6, U6.1, U6.8, U6.13, U8.4, U9.5, U10.6, U13.5, U14.5
